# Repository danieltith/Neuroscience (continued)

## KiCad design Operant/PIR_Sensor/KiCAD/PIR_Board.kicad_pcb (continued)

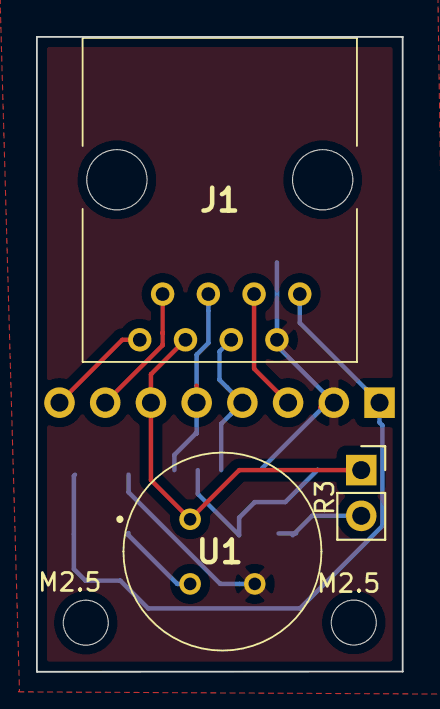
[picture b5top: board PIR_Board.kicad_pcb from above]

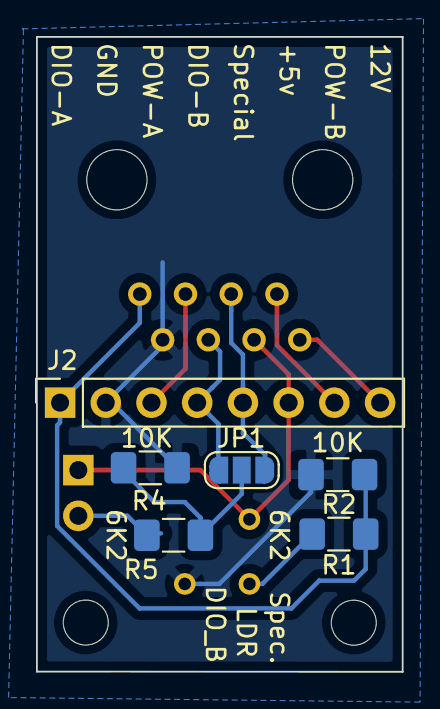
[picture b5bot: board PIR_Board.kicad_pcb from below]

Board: 2 copper layers, 20.3 x 35.3 mm, 11 parts (6 on the bottom side), 11 nets.

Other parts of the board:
M2.5, M2.5#2: MountingHole_2.5mm

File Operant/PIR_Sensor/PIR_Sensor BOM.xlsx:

Description | Quantity | Manufacturer | Manufacturer Part Number | Supplier | Supplier Part Number | Designator | Technology
RJ45 jack | 1 | AMPHENOL | 54601-908WPLF | Digikey | 609-5081-ND | J1 | THT
8 pin header (2.54mm) | 1 | Wurth Electronic | 61300811821 | Digikey | 732-61300811821-ND | J2 | THT
5V PIR sensor (AMN32111) | 1 | Panasonic | AMN32111 | Digikey | 255-2645-ND | U1 | THT
SMD resistor (6K2; 1%; 0.25W; 1206) | 2 | STACKPOLE ELECTRONICS INC (VA) | RMCF1206FT6K20 | Digikey | RMCF1206FT6K20CT-ND | R1, R5, | SMD
SMD resistor (10K; 1%; 0.5W; 1206) | 2 | STACKPOLE ELECTRONICS INC (VA) | RNCP1206FTD10K0 | Digikey | RNCP1206FTD10K0CT-ND | R2, R4 | SMD
Light Dependent Resistor | 1 |  |  |  |  | R3 | THT
Black ABS Potting Box Enclosure with Lid - 39.5x27.5x17.5mm - | 1 | Evatron | RX2006 | Farnell | EN84693 | NA | NA

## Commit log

2024-08-16 Create File Structure and Update Code
2024-08-16 Update Hardware Data
2024-08-17 CAD drawings added
    CAD drawings for operant unit added
